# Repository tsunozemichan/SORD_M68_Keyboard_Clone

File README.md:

SORD M68 Keyboard Clone Project

SORD M68のキーボードのクローンを作成するプロジェクトです。

proto04_fix_02が、M68とキーボード部分を仲介するI/F回路のKicadファイルです。

keymatrix03がキーボードのKicadファイルです。
使用しているキースイッチはCherry MX互換です。Cherry MXキースイッチのシンボル、フットプリントは様々なところで入手可能だと思います。

その他の部品のシンボルやフットプリントはLibrary Loaderで入手可能なもののみを使用していると記憶しています。

I/F回路とキーボードの接続はピンソケットになっています。
永続使用には明らかに不便ですので、ご自身で適当なコネクタに変更してください。

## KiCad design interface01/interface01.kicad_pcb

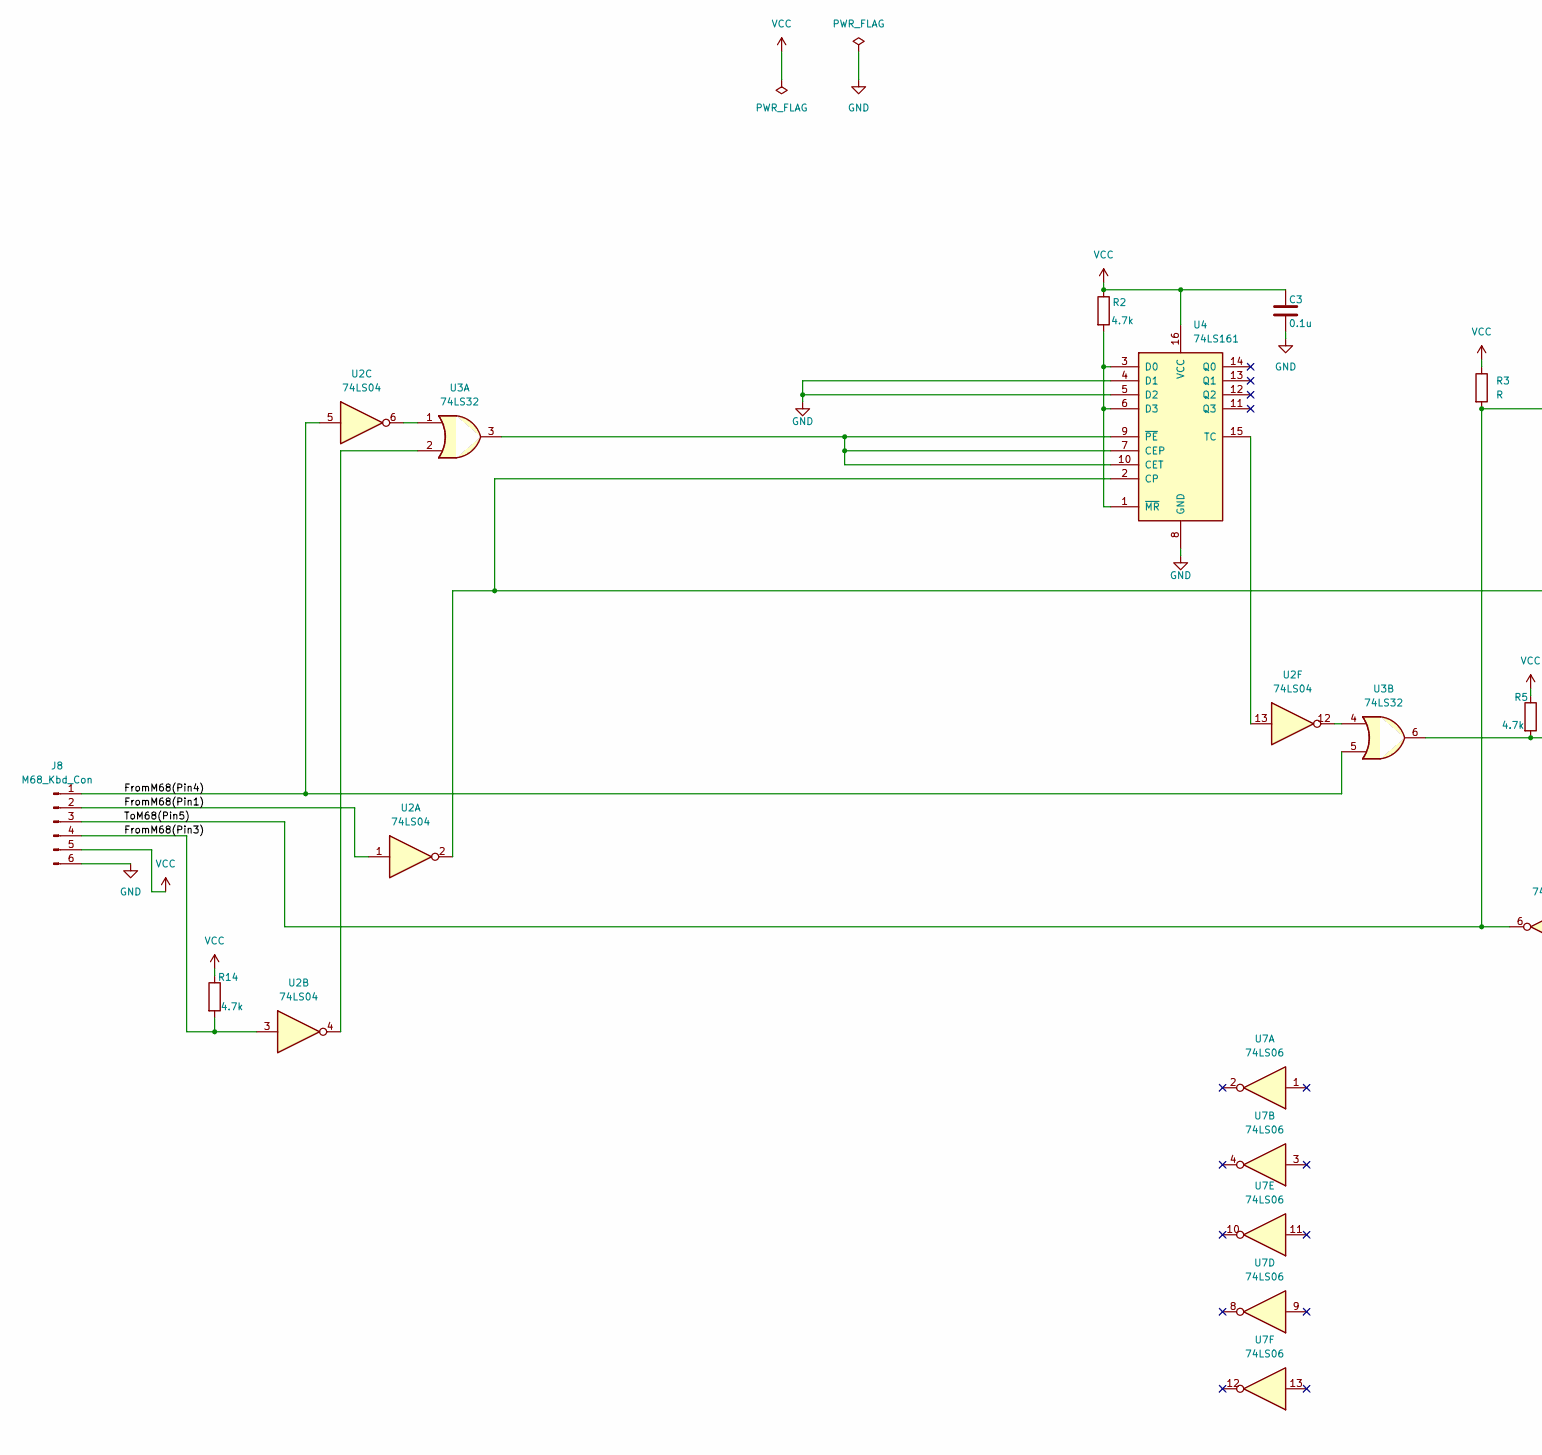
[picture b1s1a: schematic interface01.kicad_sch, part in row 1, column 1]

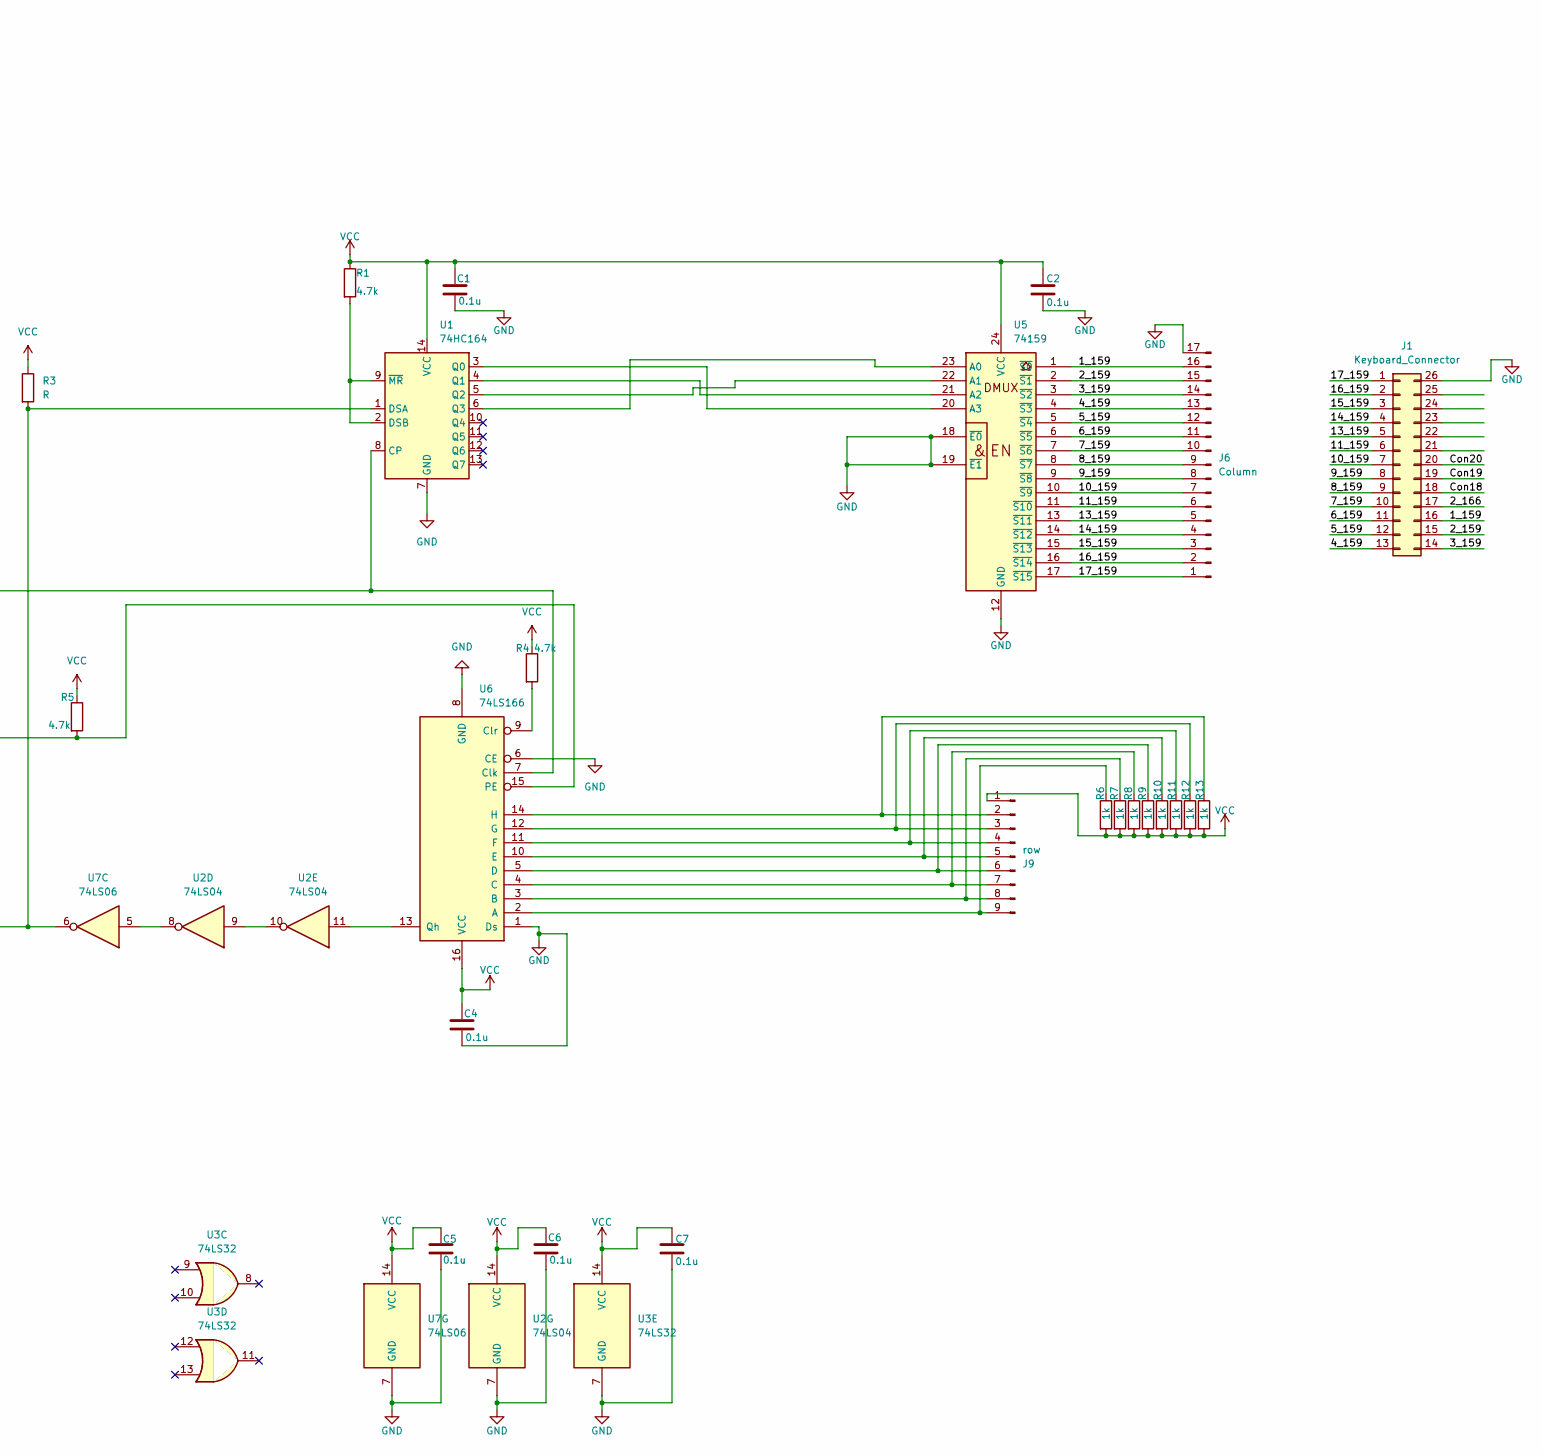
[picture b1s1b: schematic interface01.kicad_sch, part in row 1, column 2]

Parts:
C1, C2, C3, C4, C5, C6, C7: 0.1u; C_Disc_D5.0mm_W2.5mm_P2.50mm
J1: Keyboard_Connector
J6: Column; PinHeader_1x17_P2.54mm_Vertical
J8: M68_Kbd_Con; JST_XH_S6B-XH-A_1x06_P2.50mm_Horizontal
J9: row; PinHeader_1x09_P2.54mm_Vertical
R1, R2, R4, R5, R14: 4.7k; R_Axial_DIN0207_L6.3mm_D2.5mm_P10.16mm_Horizontal
R3: R; R_Axial_DIN0207_L6.3mm_D2.5mm_P10.16mm_Horizontal
R6, R7, R8, R9, R10, R11, R12, R13: 1k; R_Axial_DIN0207_L6.3mm_D2.5mm_P10.16mm_Horizontal
U1: 74HC164; DIP-14_W7.62mm_Socket_LongPads
U2: 74LS04; DIP-14_W7.62mm_Socket_LongPads
U3: 74LS32; DIP-14_W7.62mm_Socket_LongPads
U4: 74LS161; DIP-16_W7.62mm_Socket_LongPads
U5: 74159; DIP-24_W15.24mm_Socket_LongPads
U6: 74LS166; DIP-16_W7.62mm_Socket_LongPads
U7: 74LS06; DIP-14_W7.62mm_Socket_LongPads

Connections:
/FromM68(Pin1): J8.2, U2.1
/FromM68(Pin3): J8.4, R14.2, U2.3
/FromM68(Pin4): J8.1, U2.5, U3.5
/ToM68(Pin5): J8.3, R3.2, U1.1 (DSA), U7.6
GND: C1.2, C2.2, C3.2, C4.2, C5.2, C6.2, C7.2, J1.26, J6.17, J8.6, U1.7 (GND), U2.7 (GND), U3.7 (GND), U4.4 (D1), U4.5 (D2), U4.8 (GND), U5.12 (GND), U5.18 (~E0), U5.19 (~E1), U6.1 (Ds), U6.6 (CE), U6.8 (GND), U7.7 (GND)
unnamed: J1.1, J6.1, U5.17 (~S15)
unnamed: J1.2, J6.2, U5.16 (~S14)
unnamed: J1.3, J6.3, U5.15 (~S13)
unnamed: J1.4, J6.4, U5.14 (~S12)
unnamed: J1.5, J6.5, U5.13 (~S11)
unnamed: J1.6, J6.6, U5.11 (~S10)
unnamed: J1.7, J6.7, U5.10 (~S9)
unnamed: J1.8, J6.8, U5.9 (~S8)
unnamed: J1.9, J6.9, U5.8 (~S7)
unnamed: J1.10, J6.10, U5.7 (~S6)
unnamed: J1.11, J6.11, U5.6 (~S5)
unnamed: J1.12, J6.12, U5.5 (~S4)
unnamed: J1.13, J6.13, U5.4 (~S3)
unnamed: J1.14, J6.14, U5.3 (~S2)
unnamed: J1.15, J6.15, U5.2 (~S1)
unnamed: J1.16, J6.16, U5.1 (~S0)
unnamed: J9.2, R13.1, U6.14 (H)
unnamed: J9.3, R12.1, U6.12 (G)
unnamed: J9.4, R11.1, U6.11 (F)
unnamed: J9.5, R10.1, U6.10 (E)
unnamed: J9.6, R9.1, U6.5 (D)
unnamed: J9.7, R8.1, U6.4 (C)
unnamed: J9.8, R7.1, U6.3 (B)
unnamed: J9.9, R6.1, U6.2 (A)
unnamed: U1.8 (CP), U2.2, U4.2 (CP), U6.7 (Clk)
unnamed: R1.2, U1.2 (DSB), U1.9 (~MR)
unnamed: U1.3 (Q0), U5.20 (A3)
unnamed: U1.4 (Q1), U5.21 (A2)
unnamed: U1.5 (Q2), U5.22 (A1)
unnamed: U1.6 (Q3), U5.23 (A0)
unnamed: U2.4, U3.2
unnamed: U2.6, U3.1
unnamed: U2.8, U7.5
unnamed: U2.9, U2.10
unnamed: U2.12, U3.4
unnamed: U3.3, U4.7 (CEP), U4.9 (~PE), U4.10 (CET)
unnamed: R2.2, U4.1 (~MR), U4.3 (D0), U4.6 (D3)
unnamed: U2.13, U4.15 (TC)
unnamed: R4.2, U6.9 (Clr)
unnamed: R5.2, U3.6, U6.15 (PE)
unnamed: U2.11, U6.13 (Qh)
VCC: C1.1, C2.1, C3.1, C4.1, C5.1, C6.1, C7.1, J8.5, J9.1, R1.1, R2.1, R3.1, R4.1, R5.1, R6.2, R7.2, R8.2, R9.2, R10.2, R11.2, R12.2, R13.2, R14.1, U1.14 (VCC), U2.14 (VCC), U3.14 (VCC), U4.16 (VCC), U5.24 (VCC), U6.16 (VCC), U7.14 (VCC)

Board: 2 copper layers, 31 parts (0 on the bottom side), 47 nets, no tracks yet.

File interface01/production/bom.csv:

Designator,Footprint,Quantity,Value,LCSC Part #
"C1, C2, C3, C4, C5, C6, C7",C_Disc_D5.0mm_W2.5mm_P2.50mm,7,0.1u,
J6,PinHeader_1x17_P2.54mm_Vertical,1,Column,
J8,JST_XH_S6B-XH-A_1x06_P2.50mm_Horizontal,1,M68_Kbd_Con,
J9,PinHeader_1x09_P2.54mm_Vertical,1,row,
"R1, R14, R2, R4, R5",R_Axial_DIN0207_L6.3mm_D2.5mm_P10.16mm_Horizontal,5,4.7k,
"R10, R11, R12, R13, R6, R7, R8, R9",R_Axial_DIN0207_L6.3mm_D2.5mm_P10.16mm_Horizontal,8,1k,
R3,R_Axial_DIN0207_L6.3mm_D2.5mm_P10.16mm_Horizontal,1,R,
U1,DIP-14_W7.62mm_Socket_LongPads,1,74HC164,
U2,DIP-14_W7.62mm_Socket_LongPads,1,74LS04,
U3,DIP-14_W7.62mm_Socket_LongPads,1,74LS32,
U4,DIP-16_W7.62mm_Socket_LongPads,1,74LS161,
U5,DIP-24_W15.24mm_Socket_LongPads,1,74159,
U6,DIP-16_W7.62mm_Socket_LongPads,1,74LS166,
U7,DIP-14_W7.62mm_Socket_LongPads,1,74LS06,

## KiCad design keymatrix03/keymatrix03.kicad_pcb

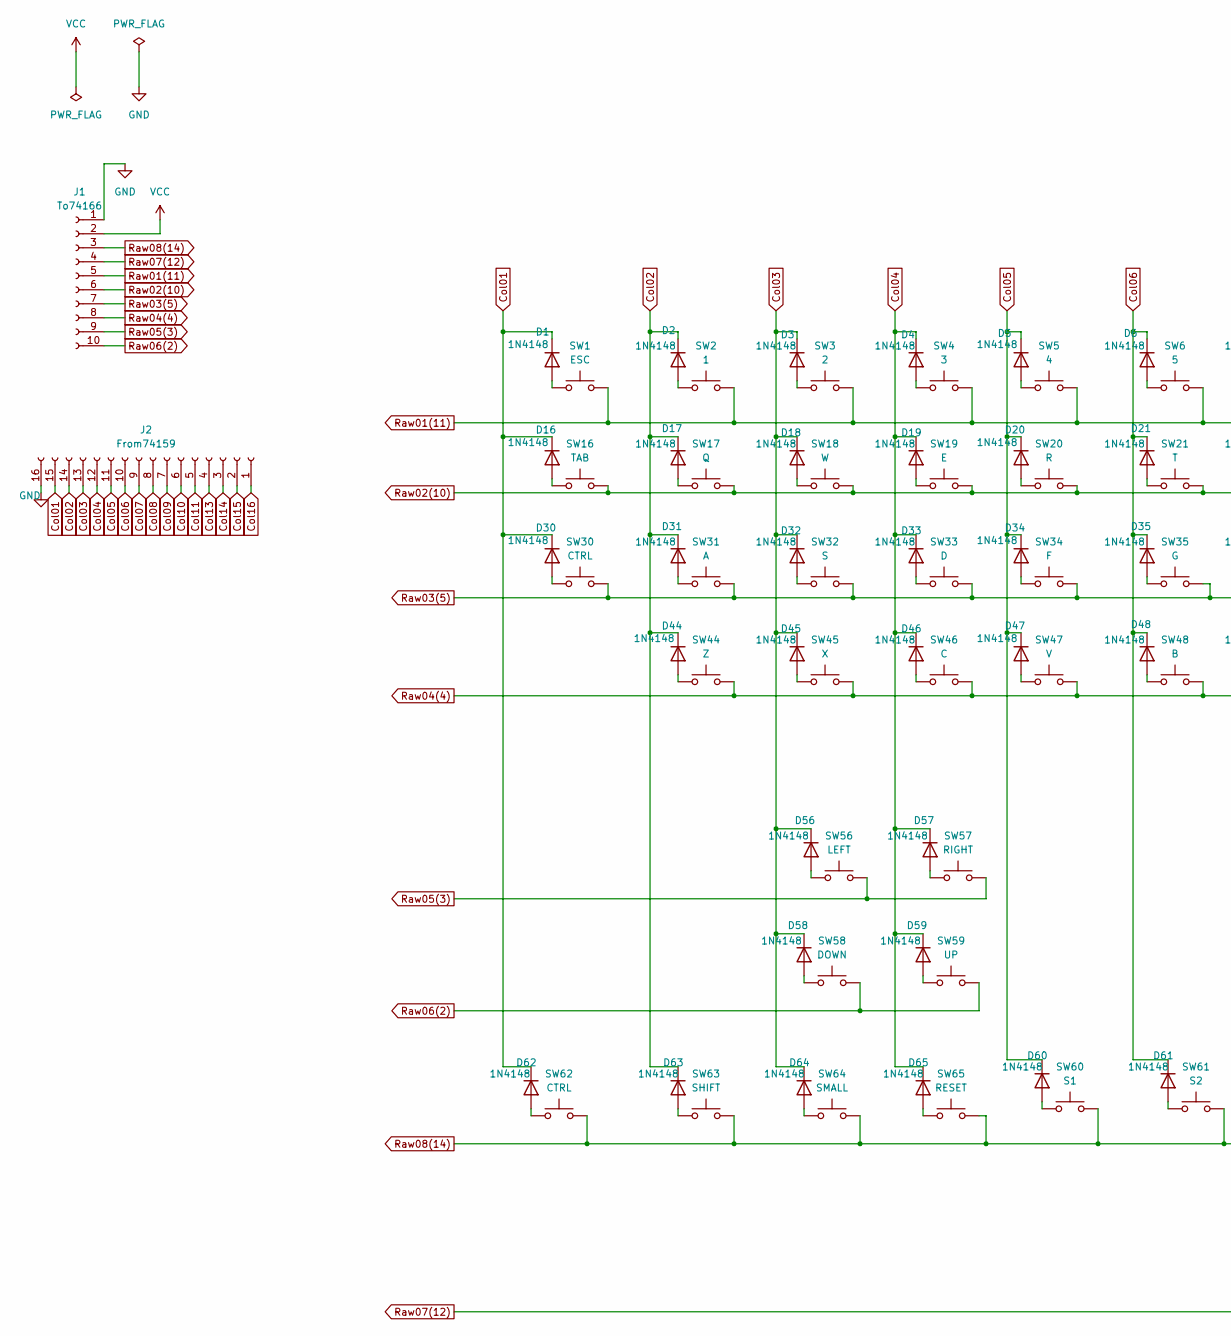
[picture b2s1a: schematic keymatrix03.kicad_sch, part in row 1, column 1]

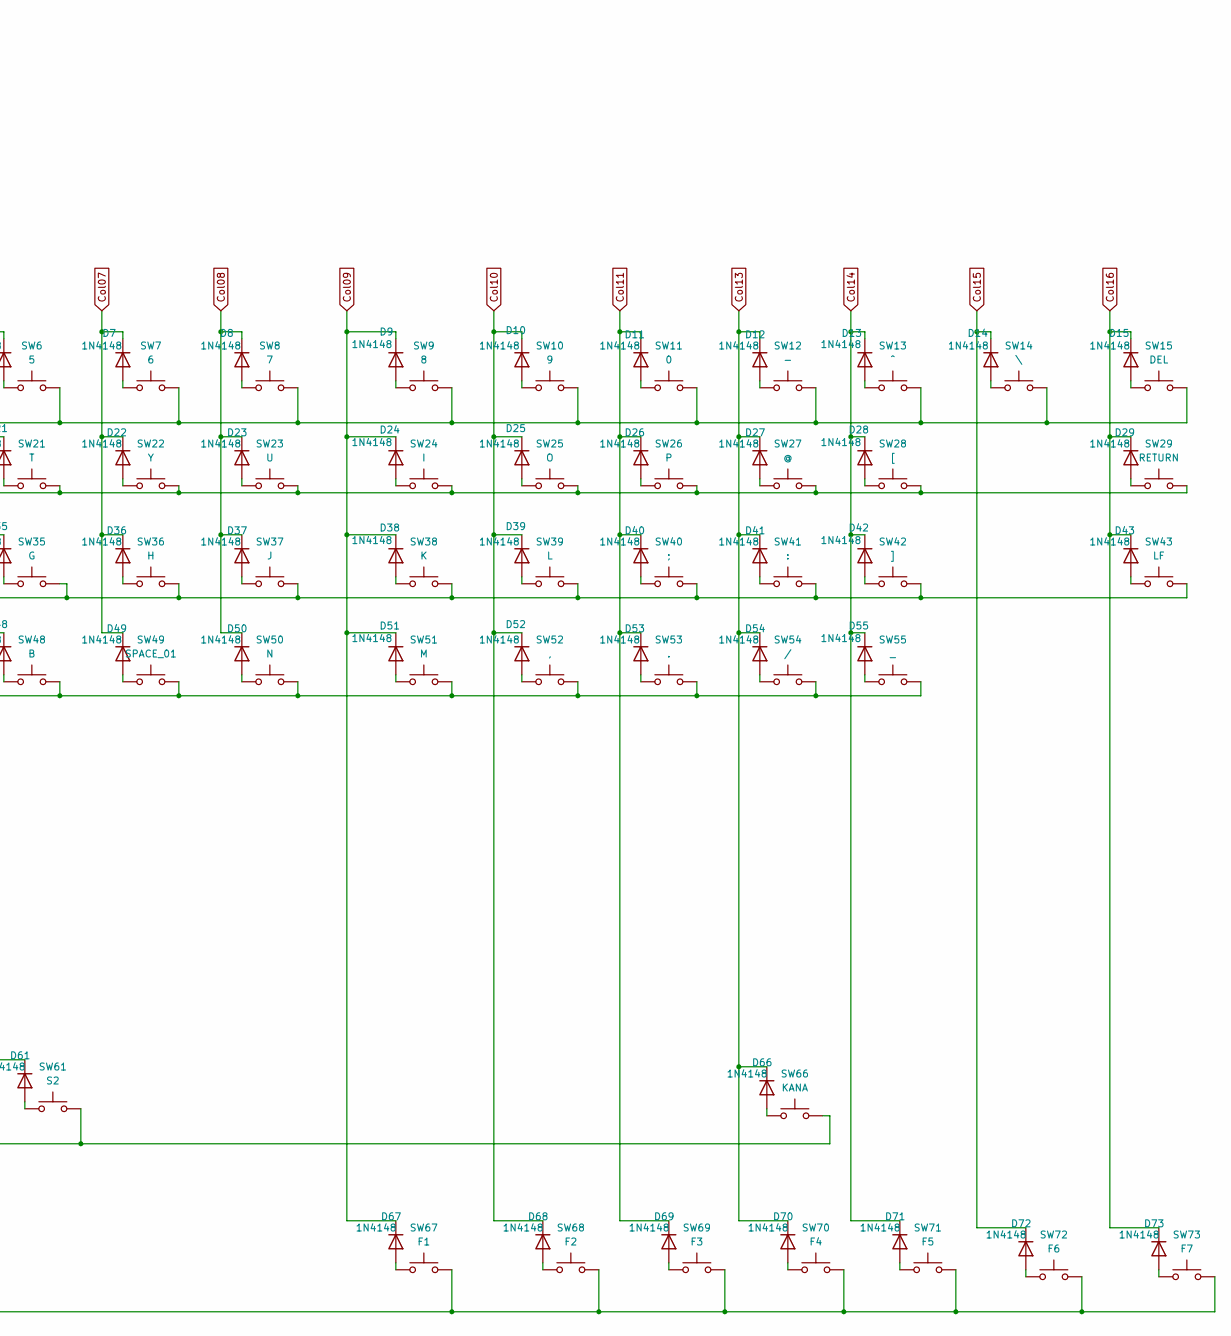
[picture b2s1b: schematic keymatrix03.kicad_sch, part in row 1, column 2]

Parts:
D1, D2, D3, D4, D5, D6, D7, D8, D9, D10, D11, D12, D13, D14, D15, D16, D17, D18, D19, D20, D21, D22, D23, D24, D25, D26, D27, D28, D29, D30, D31, D32, D33, D34, D35, D36, D37, D38, D39, D40, D41, D42, D43, D44, D45, D46, D47, D48, D49, D50, D51, D52, D53, D54, D55, D56, D57, D58, D59, D60, D61, D62, D63, D64, D65, D66, D67, D68, D69, D70, D71, D72, D73: 1N4148; D_DO-35_SOD27_P7.62mm_Horizontal
J1: To74166; PinSocket_1x10_P2.54mm_Horizontal
J2: From74159; PinSocket_1x16_P2.54mm_Horizontal
SW1: ESC; CherryMX_Red
SW2: 1; CherryMX_Red
SW3: 2; CherryMX_Red
SW4: 3; CherryMX_Red
SW5: 4; CherryMX_Red
SW6: 5; CherryMX_Red
SW7: 6; CherryMX_Red
SW8: 7; CherryMX_Red
SW9: 8; CherryMX_Red
SW10: 9; CherryMX_Red
SW11: 0; CherryMX_Red
SW12: -; CherryMX_Red
SW13: ^; CherryMX_Red
SW14: \; CherryMX_Red
SW15: DEL; CherryMX_Red
SW16: TAB; CherryMX_Red
SW17: Q; CherryMX_Red
SW18: W; CherryMX_Red
SW19: E; CherryMX_Red
SW20: R; CherryMX_Red
SW21: T; CherryMX_Red
SW22: Y; CherryMX_Red
SW23: U; CherryMX_Red
SW24: I; CherryMX_Red
SW25: O; CherryMX_Red
SW26: P; CherryMX_Red
SW27: @; CherryMX_Red
SW28: [; CherryMX_Red
SW29: RETURN; CherryMX_Red
SW30, SW62: CTRL; CherryMX_Red
SW31: A; CherryMX_Red
SW32: S; CherryMX_Red
SW33: D; CherryMX_Red
SW34: F; CherryMX_Red
SW35: G; CherryMX_Red
SW36: H; CherryMX_Red
SW37: J; CherryMX_Red
SW38: K; CherryMX_Red
SW39: L; CherryMX_Red
SW40: ;; CherryMX_Red
SW41: :; CherryMX_Red
SW42: ]; CherryMX_Red
SW43: LF; CherryMX_Red
SW44: Z; CherryMX_Red
SW45: X; CherryMX_Red
SW46: C; CherryMX_Red
SW47: V; CherryMX_Red
SW48: B; CherryMX_Red
SW49: SPACE_01; CherryMX_Red
SW50: N; CherryMX_Red
SW51: M; CherryMX_Red
SW52: ,; CherryMX_Red
SW53: .; CherryMX_Red
SW54: /; CherryMX_Red
SW55: _; CherryMX_Red
SW56: LEFT; CherryMX_Red
SW57: RIGHT; CherryMX_Red
SW58: DOWN; CherryMX_Red
SW59: UP; CherryMX_Red
SW60: S1; CherryMX_Red
SW61: S2; CherryMX_Red
SW63: SHIFT; CherryMX_Red
SW64: SMALL; CherryMX_Red
SW65: RESET; CherryMX_Red
SW66: KANA; CherryMX_Red
SW67: F1; CherryMX_Red
SW68: F2; CherryMX_Red
SW69: F3; CherryMX_Red
SW70: F4; CherryMX_Red
SW71: F5; CherryMX_Red
SW72: F6; CherryMX_Red
SW73: F7; CherryMX_Red

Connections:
Col01: D1.1 (K), D16.1 (K), D30.1 (K), D62.1 (K), J2.15
Col02: D2.1 (K), D17.1 (K), D31.1 (K), D44.1 (K), D63.1 (K), J2.14
Col03: D3.1 (K), D18.1 (K), D32.1 (K), D45.1 (K), D56.1 (K), D58.1 (K), D64.1 (K), J2.13
Col04: D4.1 (K), D19.1 (K), D33.1 (K), D46.1 (K), D57.1 (K), D59.1 (K), D65.1 (K), J2.12
Col05: D5.1 (K), D20.1 (K), D34.1 (K), D47.1 (K), D60.1 (K), J2.11
Col06: D6.1 (K), D21.1 (K), D35.1 (K), D48.1 (K), D61.1 (K), J2.10
Col07: D7.1 (K), D22.1 (K), D36.1 (K), D49.1 (K), J2.9
Col08: D8.1 (K), D23.1 (K), D37.1 (K), D50.1 (K), J2.8
Col09: D9.1 (K), D24.1 (K), D38.1 (K), D51.1 (K), D67.1 (K), J2.7
Col10: D10.1 (K), D25.1 (K), D39.1 (K), D52.1 (K), D68.1 (K), J2.6
Col11: D11.1 (K), D26.1 (K), D40.1 (K), D53.1 (K), D69.1 (K), J2.5
Col13: D12.1 (K), D27.1 (K), D41.1 (K), D54.1 (K), D66.1 (K), D70.1 (K), J2.4
Col14: D13.1 (K), D28.1 (K), D42.1 (K), D55.1 (K), D71.1 (K), J2.3
Col15: D14.1 (K), D72.1 (K), J2.2
Col16: D15.1 (K), D29.1 (K), D43.1 (K), D73.1 (K), J2.1
GND: J1.1, J2.16
unnamed: D1.2 (A), SW1.1
unnamed: D2.2 (A), SW2.1
unnamed: D3.2 (A), SW3.1
unnamed: D4.2 (A), SW4.1
unnamed: D5.2 (A), SW5.1
unnamed: D6.2 (A), SW6.1
unnamed: D7.2 (A), SW7.1
unnamed: D8.2 (A), SW8.1
unnamed: D9.2 (A), SW9.1
unnamed: D10.2 (A), SW10.1
unnamed: D11.2 (A), SW11.1
unnamed: D12.2 (A), SW12.1
unnamed: D13.2 (A), SW13.1
unnamed: D14.2 (A), SW14.1
unnamed: D15.2 (A), SW15.1
unnamed: D16.2 (A), SW16.1
unnamed: D17.2 (A), SW17.1
unnamed: D18.2 (A), SW18.1
unnamed: D19.2 (A), SW19.1
unnamed: D20.2 (A), SW20.1
unnamed: D21.2 (A), SW21.1
unnamed: D22.2 (A), SW22.1
unnamed: D23.2 (A), SW23.1
unnamed: D24.2 (A), SW24.1
unnamed: D25.2 (A), SW25.1
unnamed: D26.2 (A), SW26.1
unnamed: D27.2 (A), SW27.1
unnamed: D28.2 (A), SW28.1
unnamed: D29.2 (A), SW29.1
unnamed: D30.2 (A), SW30.1
unnamed: D31.2 (A), SW31.1
unnamed: D32.2 (A), SW32.1
unnamed: D33.2 (A), SW33.1
unnamed: D34.2 (A), SW34.1
unnamed: D35.2 (A), SW35.1
unnamed: D36.2 (A), SW36.1
unnamed: D37.2 (A), SW37.1
unnamed: D38.2 (A), SW38.1
unnamed: D39.2 (A), SW39.1
unnamed: D40.2 (A), SW40.1
unnamed: D41.2 (A), SW41.1
unnamed: D42.2 (A), SW42.1
unnamed: D43.2 (A), SW43.1
unnamed: D44.2 (A), SW44.1
unnamed: D45.2 (A), SW45.1
unnamed: D46.2 (A), SW46.1
unnamed: D47.2 (A), SW47.1
unnamed: D48.2 (A), SW48.1
unnamed: D49.2 (A), SW49.1
unnamed: D50.2 (A), SW50.1
unnamed: D51.2 (A), SW51.1
unnamed: D52.2 (A), SW52.1
unnamed: D53.2 (A), SW53.1
unnamed: D54.2 (A), SW54.1
unnamed: D55.2 (A), SW55.1
unnamed: D56.2 (A), SW56.1
unnamed: D57.2 (A), SW57.1
unnamed: D58.2 (A), SW58.1
unnamed: D59.2 (A), SW59.1
unnamed: D60.2 (A), SW60.1
unnamed: D61.2 (A), SW61.1
unnamed: D62.2 (A), SW62.1
unnamed: D63.2 (A), SW63.1
unnamed: D64.2 (A), SW64.1
unnamed: D65.2 (A), SW65.1
unnamed: D66.2 (A), SW66.1
unnamed: D67.2 (A), SW67.1
unnamed: D68.2 (A), SW68.1
unnamed: D69.2 (A), SW69.1
unnamed: D70.2 (A), SW70.1
unnamed: D71.2 (A), SW71.1
unnamed: D72.2 (A), SW72.1
unnamed: D73.2 (A), SW73.1
Raw01(11): J1.5, SW1.2, SW2.2, SW3.2, SW4.2, SW5.2, SW6.2, SW7.2, SW8.2, SW9.2, SW10.2, SW11.2, SW12.2, SW13.2, SW14.2, SW15.2
Raw02(10): J1.6, SW16.2, SW17.2, SW18.2, SW19.2, SW20.2, SW21.2, SW22.2, SW23.2, SW24.2, SW25.2, SW26.2, SW27.2, SW28.2, SW29.2
Raw03(5): J1.7, SW30.2, SW31.2, SW32.2, SW33.2, SW34.2, SW35.2, SW36.2, SW37.2, SW38.2, SW39.2, SW40.2, SW41.2, SW42.2, SW43.2
Raw04(4): J1.8, SW44.2, SW45.2, SW46.2, SW47.2, SW48.2, SW49.2, SW50.2, SW51.2, SW52.2, SW53.2, SW54.2, SW55.2
Raw05(3): J1.9, SW56.2, SW57.2
Raw06(2): J1.10, SW58.2, SW59.2
Raw07(12): J1.4, SW67.2, SW68.2, SW69.2, SW70.2, SW71.2, SW72.2, SW73.2
Raw08(14): J1.3, SW60.2, SW61.2, SW62.2, SW63.2, SW64.2, SW65.2, SW66.2
VCC: J1.2

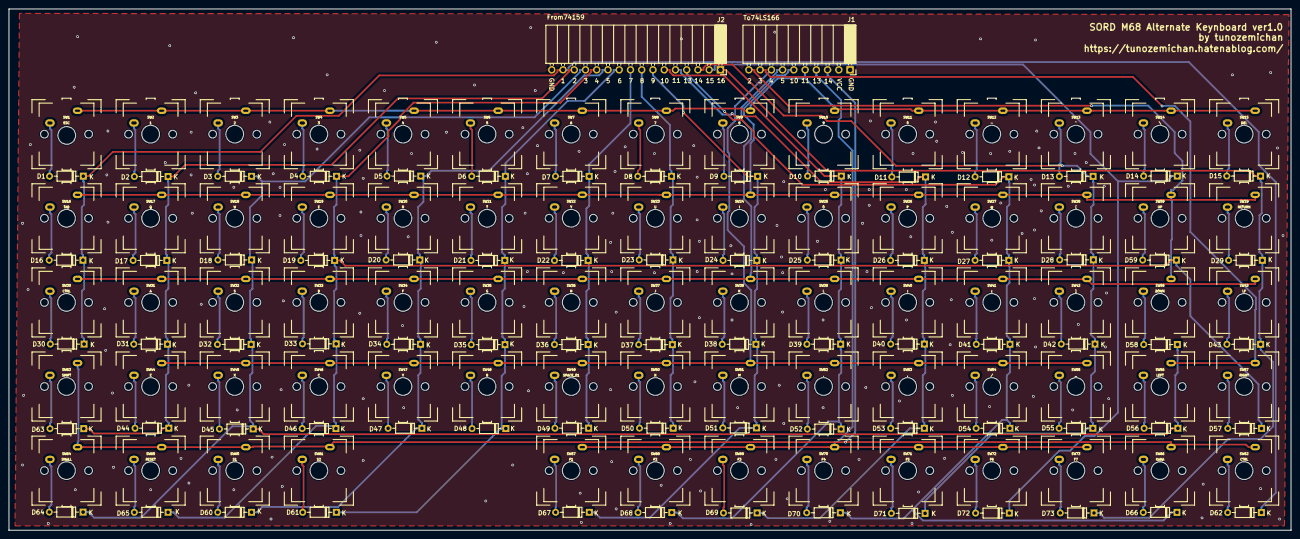
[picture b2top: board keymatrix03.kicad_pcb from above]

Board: 2 copper layers, 289.6 x 117.8 mm, 148 parts (0 on the bottom side), 97 nets.

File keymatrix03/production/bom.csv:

Designator,Footprint,Quantity,Value,LCSC Part #
"D1, D10, D11, D12, D13, D14, D15, D16, D17, D18, D19, D2, D20, D21, D22, D23, D24, D25, D26, D27, D28, D29, D3, D30, D31, D32, D33, D34, D35, D36, D37, D38, D39, D4, D40, D41, D42, D43, D44, D45, D46, D47, D48, D49, D5, D50, D51, D52, D53, D54, D55, D56, D57, D58, D59, D6, D60, D61, D62, D63, D64, D65, D66, D67, D68, D69, D7, D70, D71, D72, D73, D8, D9",D_DO-35_SOD27_P7.62mm_Horizontal,73,1N4148,
J1,PinSocket_1x10_P2.54mm_Horizontal,1,To74166,
J2,PinSocket_1x16_P2.54mm_Horizontal,1,From74159,
SW1,CherryMX_Red,1,ESC,
SW10,CherryMX_Red,1,9,
SW11,CherryMX_Red,1,0,
SW12,CherryMX_Red,1,-,
SW13,CherryMX_Red,1,^,
SW14,CherryMX_Red,1,\,
SW15,CherryMX_Red,1,DEL,
SW16,CherryMX_Red,1,TAB,
SW17,CherryMX_Red,1,Q,
SW18,CherryMX_Red,1,W,
SW19,CherryMX_Red,1,E,
SW2,CherryMX_Red,1,1,
SW20,CherryMX_Red,1,R,
SW21,CherryMX_Red,1,T,
SW22,CherryMX_Red,1,Y,
SW23,CherryMX_Red,1,U,
SW24,CherryMX_Red,1,I,
SW25,CherryMX_Red,1,O,
SW26,CherryMX_Red,1,P,
SW27,CherryMX_Red,1,@,
SW28,CherryMX_Red,1,[,
SW29,CherryMX_Red,1,RETURN,
SW3,CherryMX_Red,1,2,
"SW30, SW62",CherryMX_Red,2,CTRL,
SW31,CherryMX_Red,1,A,
SW32,CherryMX_Red,1,S,
SW33,CherryMX_Red,1,D,
SW34,CherryMX_Red,1,F,
SW35,CherryMX_Red,1,G,
SW36,CherryMX_Red,1,H,
SW37,CherryMX_Red,1,J,
SW38,CherryMX_Red,1,K,
SW39,CherryMX_Red,1,L,
SW4,CherryMX_Red,1,3,
SW40,CherryMX_Red,1,;,
SW41,CherryMX_Red,1,:,
SW42,CherryMX_Red,1,],
SW43,CherryMX_Red,1,LF,
SW44,CherryMX_Red,1,Z,
SW45,CherryMX_Red,1,X,
SW46,CherryMX_Red,1,C,
SW47,CherryMX_Red,1,V,
SW48,CherryMX_Red,1,B,
SW49,CherryMX_Red,1,SPACE_01,
SW5,CherryMX_Red,1,4,
SW50,CherryMX_Red,1,N,
SW51,CherryMX_Red,1,M,
SW52,CherryMX_Red,1,",",
SW53,CherryMX_Red,1,.,
SW54,CherryMX_Red,1,/,
SW55,CherryMX_Red,1,_,
SW56,CherryMX_Red,1,LEFT,
SW57,CherryMX_Red,1,RIGHT,
SW58,CherryMX_Red,1,DOWN,
SW59,CherryMX_Red,1,UP,
SW6,CherryMX_Red,1,5,
SW60,CherryMX_Red,1,S1,
SW61,CherryMX_Red,1,S2,
SW63,CherryMX_Red,1,SHIFT,
SW64,CherryMX_Red,1,SMALL,
SW65,CherryMX_Red,1,RESET,
SW66,CherryMX_Red,1,KANA,
SW67,CherryMX_Red,1,F1,
SW68,CherryMX_Red,1,F2,
SW69,CherryMX_Red,1,F3,
SW7,CherryMX_Red,1,6,
SW70,CherryMX_Red,1,F4,
SW71,CherryMX_Red,1,F5,
SW72,CherryMX_Red,1,F6,
SW73,CherryMX_Red,1,F7,
SW8,CherryMX_Red,1,7,
SW9,CherryMX_Red,1,8,

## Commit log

2025-04-20 Add files via upload
    First Release version. This version has been tested on a real device.
2025-06-16 add interface01
